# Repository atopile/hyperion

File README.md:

<p align="center">Insanely bright modular LED display</p>

### *** IN DEVELOPMENT ***
Project is currently in development and may not compile with latest compiler.

### Why

Current LED matrix displays are underwhelming: low brightness, low dynamic range, and washed‑out visuals in real venues. Hyperion flips that on its head with ridiculous luminance, high refresh, and a visual language that holds up in fog, dark, and daylight spill.

### Highlights

- **Blinding brightness**: designed to punch through haze and stage lighting
- **High refresh**: > 500 Hz target for artifact‑free motion and strobes
- **Chunky pixels**: 4 LEDs per pixel, **15 mm pitch** for bold geometry
- **Modular**: building full **420 × 420 mm** panels (limited by JLC assembly)
- **Controls**: video stream input (WIP) + DMX for audio‑sync (planned)

### Status

- We’ve built an initial coupon: **60 × 60 mm**, peak measured draw ~ **42 W**
- Driver: Macroblock **MBI5043** current sink
- Power rails: LED 5–17 V, logic 5 V / 3.3 V
- Hardware source is being reconstructed in ato v2 from the pixel upward.
  Pixel, pixel-row, cluster, and cluster-row qualification builds are present;
  the dual-row, controller, and complete panel hierarchy remain in progress.

### Hardware source

The root `ato.yaml` is the ato-v2 project. Physical parts resolve through the
v2 library server rather than vendored component assets. The migration is
validated bottom-up using the individual build targets before each layer is
connected into the full panel.

The shared active-low snake-data enable boundary is modeled separately in
`modules/snake_enable_distribution.ato`: one 3.3 V-to-5 V translator drives
seven 5 V-referenced NC7SZ125 enable inputs and defaults them disabled with a
pull-up.

### Pixel geometry

- **Pitch**: 15 mm → ~66 px/m in each axis → ~4,444 px/m²
- **LEDs per pixel**: 4 (RGBW cluster) → ~17,776 LEDs/m²
- **Look**: deliberately low‑density, high‑punch “big voxel” aesthetic

### How bright is it? A back‑of‑the‑napkin estimate

- Coupon area A = 60 mm × 60 mm = **0.0036 m²**
- Peak power P ≈ **42 W**
- If LED efficacy η ≈ **60–100 lm/W** (RGBW mix, conservative):
  - Luminous exitance M ≈ P·η/A ≈ 0.94–1.17 × 10⁶ lm/m²
  - Luminance L ≈ M/π ≈ **220k–370k nits**
- Compared to MacBook Pro (XDR): typical SDR ~500 nits; HDR sustained ~1,000 nits; peak ~1,600 nits. Hyperion coupon (est.): **~140×–700× brighter** per unit area.
  - Peak power assumes ~1% duty cycle for bright strobe effects or fractional‑panel use; not continuous.

Note: 42 W on 0.0036 m² implies ~11.7 kW/m² at full blast. Scaled to a **3 × 2 m** panel: ~**70–75 kW** peak. This is a thermal and power‑distribution thought experiment, not a duty‑cycle recommendation.

### Light as an underexplored rave medium

Light isn’t just illumination; it’s a volumetric instrument. Hyperion treats photons like sound—sculpted in space, time, and intensity—to cut through haze and occupy the room, not just the wall.

- Spatial volume: beams and voxels that read in fog, from meters away
- Temporal punch: sub‑ms strobes and decay envelopes, not just fades
- Materiality: bold pixels and high luminance over fine‑pitch “screens”
- Emergence: interference, moiré, and wavefronts that breathe with the music

### Roadmap

- Assemble first **420 × 420 mm** panels
- Ingest **video streams** (software pipeline WIP)
- **DMX** input for lighting desk sync and audio‑reactive modes
- Thermal, PSU, and duty‑cycle constraints for safe operation
- Thermal/power R&D: explore bulk energy storage (caps/supercaps) for strobe transients and peak handling
- Distributed temperature sensing across panels (NTC grid or digital sensors) for thermal maps and throttling

### License

MIT

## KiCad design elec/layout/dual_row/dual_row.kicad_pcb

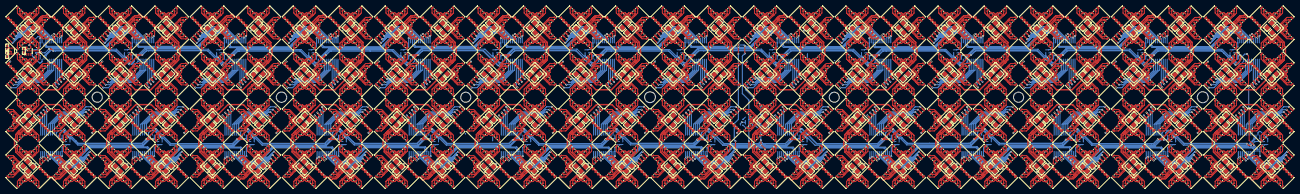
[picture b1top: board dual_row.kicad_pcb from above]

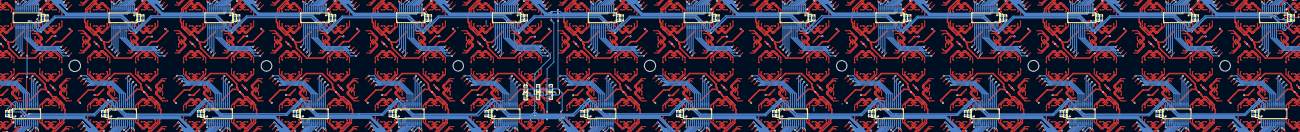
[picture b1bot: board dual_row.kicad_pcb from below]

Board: 2 copper layers, 882 parts (93 on the bottom side), 1856 nets.

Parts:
C1, C2, C3, C4, C5, C6, C7, C8, C10, C11, C12, C13, C14, C15, C16, C17, C19, C20, C21, C22, C23, C24, C25, C26, C28, C29, C30, C31, C32, C33, C34, C35, C37, C38, C39, C40, C41, C42, C43, C44, C46, C47, C48, C49, C50, C51, C52, C53, C55, C56, C57, C58, C59, C60, C61, C62, C64, C65, C66, C67, C68, C69, C70, C71, C73, C74, C75, C76, C77, C78, C79, C80, C82, C83, C84, C85, C86, C87, C88, C89, C91, C92, C93, C94, C95, C96, C97, C98, C100, C101, C102, C103, C104, C105, C106, C107, C109, C110, C111, C112, C113, C114, C115, C116, C118, C119, C120, C121, C122, C123, C124, C125, C127, C128, C129, C130, C131, C132, C133, C134, C136, C137, C138, C139, C140, C141, C142, C143, C145, C146, C147, C148, C149, C150, C151, C152, C154, C155, C156, C157, C158, C159, C160, C161, C163, C164, C165, C166, C167, C168, C169, C170, C172, C173, C174, C175, C176, C177, C178, C179, C181, C182, C183, C184, C185, C186, C187, C188, C190, C191, C192, C193, C194, C195, C196, C197, C199, C200, C201, C202, C203, C204, C205, C206, C208, C209, C210, C211, C212, C213, C214, C215, C217, C218, C219, C220, C221, C222, C223, C224, C226, C227, C228, C229, C230, C231, C232, C233, C235, C236, C237, C238, C239, C240, C241, C242, C244, C245, C246, C247, C248, C249, C250, C251: 10µF ±10% 25V X5R; C0805
C9, C18, C27, C36, C45, C54, C63, C72, C81, C90, C99, C108, C117, C126, C135, C144, C153, C162, C171, C180, C189, C198, C207, C216, C225, C234, C243, C252, C253, C254, C255, C256, C257, C258, C259, C260, C261: 100nF ±10% 16V X7R; C0402
LED1, LED2, LED3, LED4, LED5, LED6, LED7, LED8, LED9, LED10, LED11, LED12, LED13, LED14, LED15, LED16, LED17, LED18, LED19, LED20, LED21, LED22, LED23, LED24, LED25, LED26, LED27, LED28, LED29, LED30, LED31, LED32, LED33, LED34, LED35, LED36, LED37, LED38, LED39, LED40, LED41, LED42, LED43, LED44, LED45, LED46, LED47, LED48, LED49, LED50, LED51, LED52, LED53, LED54, LED55, LED56, LED57, LED58, LED59, LED60, LED61, LED62, LED63, LED64, LED65, LED66, LED67, LED68, LED69, LED70, LED71, LED72, LED73, LED74, LED75, LED76, LED77, LED78, LED79, LED80, LED81, LED82, LED83, LED84, LED85, LED86, LED87, LED88, LED89, LED90, LED91, LED92, LED93, LED94, LED95, LED96, LED97, LED98, LED99, LED100, LED101, LED102, LED103, LED104, LED105, LED106, LED107, LED108, LED109, LED110, LED111, LED112, LED113, LED114, LED115, LED116, LED117, LED118, LED119, LED120, LED121, LED122, LED123, LED124, LED125, LED126, LED127, LED128, LED129, LED130, LED131, LED132, LED133, LED134, LED135, LED136, LED137, LED138, LED139, LED140, LED141, LED142, LED143, LED144, LED145, LED146, LED147, LED148, LED149, LED150, LED151, LED152, LED153, LED154, LED155, LED156, LED157, LED158, LED159, LED160, LED161, LED162, LED163, LED164, LED165, LED166, LED167, LED168, LED169, LED170, LED171, LED172, LED173, LED174, LED175, LED176, LED177, LED178, LED179, LED180, LED181, LED182, LED183, LED184, LED185, LED186, LED187, LED188, LED189, LED190, LED191, LED192, LED193, LED194, LED195, LED196, LED197, LED198, LED199, LED200, LED201, LED202, LED203, LED204, LED205, LED206, LED207, LED208, LED209, LED210, LED211, LED212, LED213, LED214, LED215, LED216, LED217, LED218, LED219, LED220, LED221, LED222, LED223, LED224, LED225, LED226, LED227, LED228, LED229, LED230, LED231, LED232, LED233, LED234, LED235, LED236, LED237, LED238, LED239, LED240, LED241, LED242, LED243, LED244, LED245, LED246, LED247, LED248, LED249, LED250, LED251, LED252, LED253, LED254, LED255, LED256, LED257, LED258, LED259, LED260, LED261, LED262, LED263, LED264, LED265, LED266, LED267, LED268, LED269, LED270, LED271, LED272, LED273, LED274, LED275, LED276, LED277, LED278, LED279, LED280, LED281, LED282, LED283, LED284, LED285, LED286, LED287, LED288, LED289, LED290, LED291, LED292, LED293, LED294, LED295, LED296, LED297, LED298, LED299, LED300, LED301, LED302, LED303, LED304, LED305, LED306, LED307, LED308, LED309, LED310, LED311, LED312, LED313, LED314, LED315, LED316, LED317, LED318, LED319, LED320, LED321, LED322, LED323, LED324, LED325, LED326, LED327, LED328, LED329, LED330, LED331, LED332, LED333, LED334, LED335, LED336, LED337, LED338, LED339, LED340, LED341, LED342, LED343, LED344, LED345, LED346, LED347, LED348, LED349, LED350, LED351, LED352, LED353, LED354, LED355, LED356, LED357, LED358, LED359, LED360, LED361, LED362, LED363, LED364, LED365, LED366, LED367, LED368, LED369, LED370, LED371, LED372, LED373, LED374, LED375, LED376, LED377, LED378, LED379, LED380, LED381, LED382, LED383, LED384, LED385, LED386, LED387, LED388, LED389, LED390, LED391, LED392, LED393, LED394, LED395, LED396, LED397, LED398, LED399, LED400, LED401, LED402, LED403, LED404, LED405, LED406, LED407, LED408, LED409, LED410, LED411, LED412, LED413, LED414, LED415, LED416, LED417, LED418, LED419, LED420, LED421, LED422, LED423, LED424, LED425, LED426, LED427, LED428, LED429, LED430, LED431, LED432, LED433, LED434, LED435, LED436, LED437, LED438, LED439, LED440, LED441, LED442, LED443, LED444, LED445, LED446, LED447, LED448: LED-SMD_8P-L5.0-W5.0-P1.20_HL-5050RGBW-S1-A27
R1, R2, R3, R4, R5, R6, R7, R8, R9, R10, R11, R12, R13, R14, R15, R16, R17, R18, R19, R20, R21, R22, R23, R24, R25, R26, R27, R28: 309Ω ±1% 62.5mW; R0402
U1, U6, U11, U16, U21, U26, U31, U36, U41, U46, U51, U56, U61, U66, U71, U76, U81, U86, U91, U96, U101, U106, U111, U116, U121, U126, U131, U136: SSOP-24_L8.8-W4.0-P0.64-LS6.2-BL
U2, U3, U4, U5, U7, U8, U9, U10, U12, U13, U14, U15, U17, U18, U19, U20, U22, U23, U24, U25, U27, U28, U29, U30, U32, U33, U34, U35, U37, U38, U39, U40, U42, U43, U44, U45, U47, U48, U49, U50, U52, U53, U54, U55, U57, U58, U59, U60, U62, U63, U64, U65, U67, U68, U69, U70, U72, U73, U74, U75, U77, U78, U79, U80, U82, U83, U84, U85, U87, U88, U89, U90, U92, U93, U94, U95, U97, U98, U99, U100, U102, U103, U104, U105, U107, U108, U109, U110, U112, U113, U114, U115, U117, U118, U119, U120, U122, U123, U124, U125, U127, U128, U129, U130, U132, U133, U134, U135, U137, U138, U139, U140: pixel15
U141: SC-70-5_L2.1-W1.3-P0.65-LS2.1-BR
U142, U143, U144, U145: SC-70-6_L2.2-W1.3-P0.65-LS2.1-BR

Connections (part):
DCLK: U1.3, U6.3, U11.3, U16.3, U21.3, U26.3, U31.3, U36.3, U41.3, U46.3, U51.3, U56.3, U61.3, U66.3, U71.3, U76.3, U81.3, U86.3, U91.3, U96.3, U101.3, U106.3, U111.3, U116.3, U121.3, U126.3, U131.3, U136.3, U143.4
GCLK: U1.21, U6.21, U11.21, U16.21, U21.21, U26.21, U31.21, U36.21, U41.21, U46.21, U51.21, U56.21, U61.21, U66.21, U71.21, U76.21, U81.21, U86.21, U91.21, U96.21, U101.21, U106.21, U111.21, U116.21, U121.21, U126.21, U131.21, U136.21, U144.4
LE: U1.4, U6.4, U11.4, U16.4, U21.4, U26.4, U31.4, U36.4, U41.4, U46.4, U51.4, U56.4, U61.4, U66.4, U71.4, U76.4, U81.4, U86.4, U91.4, U96.4, U101.4, U106.4, U111.4, U116.4, U121.4, U126.4, U131.4, U136.4, U145.4
clusters[0]-REXT-0: R1.1, U1.23
clusters[0]-REXT-1: R15.1, U71.23
clusters[1]-REXT-0: R2.1, U6.23
clusters[1]-REXT-1: R16.1, U76.23
clusters[2]-REXT-0: R3.1, U11.23
clusters[2]-REXT-1: R17.1, U81.23
clusters[3]-REXT-0: R4.1, U16.23
clusters[3]-REXT-1: R18.1, U86.23
clusters[4]-REXT-0: R5.1, U21.23
clusters[4]-REXT-1: R19.1, U91.23
clusters[5]-REXT-0: R6.1, U26.23
clusters[5]-REXT-1: R20.1, U96.23
clusters[6]-REXT-0: R7.1, U31.23
clusters[6]-REXT-1: R21.1, U101.23
clusters[7]-REXT-0: R8.1, U36.23
clusters[7]-REXT-1: R22.1, U106.23
clusters[8]-REXT-0: R9.1, U41.23
clusters[8]-REXT-1: R23.1, U111.23
clusters[9]-REXT-0: R10.1, U46.23
clusters[9]-REXT-1: R24.1, U116.23
clusters[10]-REXT-0: R11.1, U51.23
clusters[10]-REXT-1: R25.1, U121.23
clusters[11]-REXT-0: R12.1, U56.23
clusters[11]-REXT-1: R26.1, U126.23
clusters[12]-REXT-0: R13.1, U61.23
clusters[12]-REXT-1: R27.1, U131.23
clusters[13]-REXT-0: R14.1, U66.23
clusters[13]-REXT-1: R28.1, U136.23
data_in-line: U66.22, U71.2
driver-sdo-line-0: U1.22, U6.2
driver-sdo-line-1: U46.22, U51.2
driver-sdo-line-2: U51.22, U56.2
driver-sdo-line-3: U56.22, U61.2
driver-sdo-line-4: U61.22, U66.2
driver-sdo-line-5: U6.22, U11.2
driver-sdo-line-6: U11.22, U16.2
driver-sdo-line-7: U16.22, U21.2
driver-sdo-line-8: U21.22, U26.2
driver-sdo-line-9: U26.22, U31.2
driver-sdo-line-10: U31.22, U36.2
driver-sdo-line-11: U36.22, U41.2
driver-sdo-line-12: U41.22, U46.2
driver-sdo-line-13: U71.22, U76.2
driver-sdo-line-14: U116.22, U121.2
driver-sdo-line-15: U121.22, U126.2
driver-sdo-line-16: U126.22, U131.2
driver-sdo-line-17: U131.22, U136.2
driver-sdo-line-18: U76.22, U81.2
driver-sdo-line-19: U81.22, U86.2
driver-sdo-line-20: U86.22, U91.2
driver-sdo-line-21: U91.22, U96.2
driver-sdo-line-22: U96.22, U101.2
driver-sdo-line-23: U101.22, U106.2
driver-sdo-line-24: U106.22, U111.2
driver-sdo-line-25: U111.22, U116.2
power_a-VCC: C254.1, C256.1, C258.1, C260.1, U142.1, U143.1, U143.5, U144.1, U144.5, U145.1
power_b-GND: C9.2, C18.2, C27.2, C36.2, C45.2, C54.2, C63.2, C72.2, C81.2, C90.2, C99.2, C108.2, C117.2, C126.2, C135.2, C144.2, C153.2, C162.2, C171.2, C180.2, C189.2, C198.2, C207.2, C216.2, C225.2, C234.2, C243.2, C252.2, C253.2, C254.2, C255.2, C256.2, C257.2, C258.2, C259.2, C260.2, C261.2, R1.2, R2.2, R3.2, R4.2, R5.2, R6.2, R7.2, R8.2, R9.2, R10.2, R11.2, R12.2, R13.2, R14.2, R15.2, R16.2, R17.2, R18.2, R19.2, R20.2, R21.2, R22.2, R23.2, R24.2, R25.2, R26.2, R27.2, R28.2, U1.1, U6.1, U11.1, U16.1, U21.1, U26.1, U31.1, U36.1, U41.1, U46.1, U51.1, U56.1, U61.1, U66.1, U71.1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
power_b-VCC: C9.1, C18.1, C27.1, C36.1, C45.1, C54.1, C63.1, C72.1, C81.1, C90.1, C99.1, C108.1, C117.1, C126.1, C135.1, C144.1, C153.1, C162.1, C171.1, C180.1, C189.1, C198.1, C207.1, C216.1, C225.1, C234.1, C243.1, C252.1, C253.1, C255.1, C257.1, C259.1, C261.1, U1.24, U6.24, U11.24, U16.24, U21.24, U26.24, U31.24, U36.24, U41.24, U46.24, U51.24, U56.24, U61.24, U66.24, U71.24, U76.24, U81.24, U86.24, U91.24, U96.24, U101.24, U106.24, U111.24, U116.24, U121.24, U126.24, U131.24, U136.24, U141.5, U142.6, U143.6, U144.6, U145.6
power_leds-GND: C1.2, C2.2, C3.2, C4.2, C5.2, C6.2, C7.2, C8.2, C10.2, C11.2, C12.2, C13.2, C14.2, C15.2, C16.2, C17.2, C19.2, C20.2, C21.2, C22.2, C23.2, C24.2, C25.2, C26.2, C28.2, C29.2, C30.2, C31.2, C32.2, C33.2, C34.2, C35.2, C37.2, C38.2, C39.2, C40.2, C41.2, C42.2, C43.2, C44.2, C46.2, C47.2, C48.2, C49.2, C50.2, C51.2, C52.2, C53.2, C55.2, C56.2, C57.2, C58.2, C59.2, C60.2, C61.2, C62.2, C64.2, C65.2, C66.2, C67.2, C68.2, C69.2, C70.2, C71.2, C73.2, C74.2, C75.2, C76.2, C77.2, C78.2, C79.2, C80.2, C82.2, C83.2, C84.2, C85.2, C86.2, C87.2, C88.2, C89.2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
power_leds-VCC: C1.1, C2.1, C3.1, C4.1, C5.1, C6.1, C7.1, C8.1, C10.1, C11.1, C12.1, C13.1, C14.1, C15.1, C16.1, C17.1, C19.1, C20.1, C21.1, C22.1, C23.1, C24.1, C25.1, C26.1, C28.1, C29.1, C30.1, C31.1, C32.1, C33.1, C34.1, C35.1, C37.1, C38.1, C39.1, C40.1, C41.1, C42.1, C43.1, C44.1, C46.1, C47.1, C48.1, C49.1, C50.1, C51.1, C52.1, C53.1, C55.1, C56.1, C57.1, C58.1, C59.1, C60.1, C61.1, C62.1, C64.1, C65.1, C66.1, C67.1, C68.1, C69.1, C70.1, C71.1, C73.1, C74.1, C75.1, C76.1, C77.1, C78.1, C79.1, C80.1, C82.1, C83.1, C84.1, C85.1, C86.1, C87.1, C88.1, C89.1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
rgbs[1]-anodes-anode-0: LED1.3, LED2.4
rgbs[1]-anodes-anode-1: LED1.1, LED2.2
rgbs[1]-anodes-anode-2: LED1.5, LED2.6
rgbs[1]-anodes-anode-3: LED1.7, LED2.8
rgbs[1]-anodes-anode-4: LED5.3, LED6.4
rgbs[1]-anodes-anode-5: LED5.1, LED6.2
rgbs[1]-anodes-anode-6: LED5.5, LED6.6
rgbs[1]-anodes-anode-7: LED5.7, LED6.8
rgbs[1]-anodes-anode-8: LED9.3, LED10.4
rgbs[1]-anodes-anode-9: LED9.1, LED10.2
rgbs[1]-anodes-anode-10: LED9.5, LED10.6
rgbs[1]-anodes-anode-11: LED9.7, LED10.8
rgbs[1]-anodes-anode-12: LED13.3, LED14.4
rgbs[1]-anodes-anode-13: LED13.1, LED14.2
rgbs[1]-anodes-anode-14: LED13.5, LED14.6
rgbs[1]-anodes-anode-15: LED13.7, LED14.8
rgbs[1]-anodes-anode-16: LED161.3, LED162.4
rgbs[1]-anodes-anode-17: LED161.1, LED162.2
rgbs[1]-anodes-anode-18: LED161.5, LED162.6
rgbs[1]-anodes-anode-19: LED161.7, LED162.8
rgbs[1]-anodes-anode-20: LED165.3, LED166.4
rgbs[1]-anodes-anode-21: LED165.1, LED166.2
rgbs[1]-anodes-anode-22: LED165.5, LED166.6
rgbs[1]-anodes-anode-23: LED165.7, LED166.8
rgbs[1]-anodes-anode-24: LED169.3, LED170.4
rgbs[1]-anodes-anode-25: LED169.1, LED170.2
rgbs[1]-anodes-anode-26: LED169.5, LED170.6
rgbs[1]-anodes-anode-27: LED169.7, LED170.8
rgbs[1]-anodes-anode-28: LED173.3, LED174.4
rgbs[1]-anodes-anode-29: LED173.1, LED174.2
rgbs[1]-anodes-anode-30: LED173.5, LED174.6
rgbs[1]-anodes-anode-31: LED173.7, LED174.8
rgbs[1]-anodes-anode-32: LED177.3, LED178.4
rgbs[1]-anodes-anode-33: LED177.1, LED178.2
rgbs[1]-anodes-anode-34: LED177.5, LED178.6
rgbs[1]-anodes-anode-35: LED177.7, LED178.8
rgbs[1]-anodes-anode-36: LED181.3, LED182.4
rgbs[1]-anodes-anode-37: LED181.1, LED182.2
rgbs[1]-anodes-anode-38: LED181.5, LED182.6
rgbs[1]-anodes-anode-39: LED181.7, LED182.8
rgbs[1]-anodes-anode-40: LED185.3, LED186.4
rgbs[1]-anodes-anode-41: LED185.1, LED186.2
rgbs[1]-anodes-anode-42: LED185.5, LED186.6
rgbs[1]-anodes-anode-43: LED185.7, LED186.8
rgbs[1]-anodes-anode-44: LED189.3, LED190.4
rgbs[1]-anodes-anode-45: LED189.1, LED190.2
rgbs[1]-anodes-anode-46: LED189.5, LED190.6
rgbs[1]-anodes-anode-47: LED189.7, LED190.8
rgbs[1]-anodes-anode-48: LED193.3, LED194.4
rgbs[1]-anodes-anode-49: LED193.1, LED194.2
rgbs[1]-anodes-anode-50: LED193.5, LED194.6
rgbs[1]-anodes-anode-51: LED193.7, LED194.8
rgbs[1]-anodes-anode-52: LED197.3, LED198.4
rgbs[1]-anodes-anode-53: LED197.1, LED198.2
rgbs[1]-anodes-anode-54: LED197.5, LED198.6
rgbs[1]-anodes-anode-55: LED197.7, LED198.8
rgbs[1]-anodes-anode-56: LED201.3, LED202.4
rgbs[1]-anodes-anode-57: LED201.1, LED202.2
rgbs[1]-anodes-anode-58: LED201.5, LED202.6
rgbs[1]-anodes-anode-59: LED201.7, LED202.8
rgbs[1]-anodes-anode-60: LED205.3, LED206.4
rgbs[1]-anodes-anode-61: LED205.1, LED206.2
rgbs[1]-anodes-anode-62: LED205.5, LED206.6
rgbs[1]-anodes-anode-63: LED205.7, LED206.8
rgbs[1]-anodes-anode-64: LED209.3, LED210.4
rgbs[1]-anodes-anode-65: LED209.1, LED210.2
rgbs[1]-anodes-anode-66: LED209.5, LED210.6
rgbs[1]-anodes-anode-67: LED209.7, LED210.8
rgbs[1]-anodes-anode-68: LED213.3, LED214.4
rgbs[1]-anodes-anode-69: LED213.1, LED214.2
rgbs[1]-anodes-anode-70: LED213.5, LED214.6
rgbs[1]-anodes-anode-71: LED213.7, LED214.8
rgbs[1]-anodes-anode-72: LED217.3, LED218.4
rgbs[1]-anodes-anode-73: LED217.1, LED218.2
rgbs[1]-anodes-anode-74: LED217.5, LED218.6
rgbs[1]-anodes-anode-75: LED217.7, LED218.8
rgbs[1]-anodes-anode-76: LED221.3, LED222.4
rgbs[1]-anodes-anode-77: LED221.1, LED222.2
rgbs[1]-anodes-anode-78: LED221.5, LED222.6
rgbs[1]-anodes-anode-79: LED221.7, LED222.8
rgbs[1]-anodes-anode-80: LED17.3, LED18.4
rgbs[1]-anodes-anode-81: LED17.1, LED18.2
rgbs[1]-anodes-anode-82: LED17.5, LED18.6
rgbs[1]-anodes-anode-83: LED17.7, LED18.8
rgbs[1]-anodes-anode-84: LED21.3, LED22.4
rgbs[1]-anodes-anode-85: LED21.1, LED22.2
rgbs[1]-anodes-anode-86: LED21.5, LED22.6
rgbs[1]-anodes-anode-87: LED21.7, LED22.8
rgbs[1]-anodes-anode-88: LED25.3, LED26.4
rgbs[1]-anodes-anode-89: LED25.1, LED26.2
rgbs[1]-anodes-anode-90: LED25.5, LED26.6
rgbs[1]-anodes-anode-91: LED25.7, LED26.8
rgbs[1]-anodes-anode-92: LED29.3, LED30.4
rgbs[1]-anodes-anode-93: LED29.1, LED30.2
rgbs[1]-anodes-anode-94: LED29.5, LED30.6
rgbs[1]-anodes-anode-95: LED29.7, LED30.8
rgbs[1]-anodes-anode-96: LED33.3, LED34.4
rgbs[1]-anodes-anode-97: LED33.1, LED34.2
rgbs[1]-anodes-anode-98: LED33.5, LED34.6
rgbs[1]-anodes-anode-99: LED33.7, LED34.8
rgbs[1]-anodes-anode-100: LED37.3, LED38.4
rgbs[1]-anodes-anode-101: LED37.1, LED38.2
rgbs[1]-anodes-anode-102: LED37.5, LED38.6
rgbs[1]-anodes-anode-103: LED37.7, LED38.8
rgbs[1]-anodes-anode-104: LED41.3, LED42.4
rgbs[1]-anodes-anode-105: LED41.1, LED42.2
rgbs[1]-anodes-anode-106: LED41.5, LED42.6
rgbs[1]-anodes-anode-107: LED41.7, LED42.8
rgbs[1]-anodes-anode-108: LED45.3, LED46.4
rgbs[1]-anodes-anode-109: LED45.1, LED46.2
rgbs[1]-anodes-anode-110: LED45.5, LED46.6
rgbs[1]-anodes-anode-111: LED45.7, LED46.8
rgbs[1]-anodes-anode-112: LED49.3, LED50.4
rgbs[1]-anodes-anode-113: LED49.1, LED50.2
rgbs[1]-anodes-anode-114: LED49.5, LED50.6
rgbs[1]-anodes-anode-115: LED49.7, LED50.8
rgbs[1]-anodes-anode-116: LED53.3, LED54.4
rgbs[1]-anodes-anode-117: LED53.1, LED54.2
rgbs[1]-anodes-anode-118: LED53.5, LED54.6
rgbs[1]-anodes-anode-119: LED53.7, LED54.8
rgbs[1]-anodes-anode-120: LED57.3, LED58.4
rgbs[1]-anodes-anode-121: LED57.1, LED58.2
rgbs[1]-anodes-anode-122: LED57.5, LED58.6
rgbs[1]-anodes-anode-123: LED57.7, LED58.8
rgbs[1]-anodes-anode-124: LED61.3, LED62.4
rgbs[1]-anodes-anode-125: LED61.1, LED62.2
rgbs[1]-anodes-anode-126: LED61.5, LED62.6
rgbs[1]-anodes-anode-127: LED61.7, LED62.8
rgbs[1]-anodes-anode-128: LED65.3, LED66.4
rgbs[1]-anodes-anode-129: LED65.1, LED66.2
rgbs[1]-anodes-anode-130: LED65.5, LED66.6
rgbs[1]-anodes-anode-131: LED65.7, LED66.8
rgbs[1]-anodes-anode-132: LED69.3, LED70.4
rgbs[1]-anodes-anode-133: LED69.1, LED70.2
rgbs[1]-anodes-anode-134: LED69.5, LED70.6
rgbs[1]-anodes-anode-135: LED69.7, LED70.8
rgbs[1]-anodes-anode-136: LED73.3, LED74.4
rgbs[1]-anodes-anode-137: LED73.1, LED74.2
rgbs[1]-anodes-anode-138: LED73.5, LED74.6
rgbs[1]-anodes-anode-139: LED73.7, LED74.8
rgbs[1]-anodes-anode-140: LED77.3, LED78.4
rgbs[1]-anodes-anode-141: LED77.1, LED78.2
rgbs[1]-anodes-anode-142: LED77.5, LED78.6
rgbs[1]-anodes-anode-143: LED77.7, LED78.8
rgbs[1]-anodes-anode-144: LED81.3, LED82.4
rgbs[1]-anodes-anode-145: LED81.1, LED82.2
rgbs[1]-anodes-anode-146: LED81.5, LED82.6
rgbs[1]-anodes-anode-147: LED81.7, LED82.8
rgbs[1]-anodes-anode-148: LED85.3, LED86.4
rgbs[1]-anodes-anode-149: LED85.1, LED86.2
rgbs[1]-anodes-anode-150: LED85.5, LED86.6
rgbs[1]-anodes-anode-151: LED85.7, LED86.8
rgbs[1]-anodes-anode-152: LED89.3, LED90.4
rgbs[1]-anodes-anode-153: LED89.1, LED90.2
rgbs[1]-anodes-anode-154: LED89.5, LED90.6
rgbs[1]-anodes-anode-155: LED89.7, LED90.8
rgbs[1]-anodes-anode-156: LED93.3, LED94.4
rgbs[1]-anodes-anode-157: LED93.1, LED94.2
rgbs[1]-anodes-anode-158: LED93.5, LED94.6
rgbs[1]-anodes-anode-159: LED93.7, LED94.8
rgbs[1]-anodes-anode-160: LED97.3, LED98.4
rgbs[1]-anodes-anode-161: LED97.1, LED98.2
rgbs[1]-anodes-anode-162: LED97.5, LED98.6
rgbs[1]-anodes-anode-163: LED97.7, LED98.8
rgbs[1]-anodes-anode-164: LED101.3, LED102.4
rgbs[1]-anodes-anode-165: LED101.1, LED102.2
rgbs[1]-anodes-anode-166: LED101.5, LED102.6
rgbs[1]-anodes-anode-167: LED101.7, LED102.8
rgbs[1]-anodes-anode-168: LED105.3, LED106.4
rgbs[1]-anodes-anode-169: LED105.1, LED106.2
rgbs[1]-anodes-anode-170: LED105.5, LED106.6
rgbs[1]-anodes-anode-171: LED105.7, LED106.8
rgbs[1]-anodes-anode-172: LED109.3, LED110.4
rgbs[1]-anodes-anode-173: LED109.1, LED110.2
rgbs[1]-anodes-anode-174: LED109.5, LED110.6
rgbs[1]-anodes-anode-175: LED109.7, LED110.8
rgbs[1]-anodes-anode-176: LED113.3, LED114.4
rgbs[1]-anodes-anode-177: LED113.1, LED114.2
rgbs[1]-anodes-anode-178: LED113.5, LED114.6
rgbs[1]-anodes-anode-179: LED113.7, LED114.8
rgbs[1]-anodes-anode-180: LED117.3, LED118.4
rgbs[1]-anodes-anode-181: LED117.1, LED118.2
rgbs[1]-anodes-anode-182: LED117.5, LED118.6
rgbs[1]-anodes-anode-183: LED117.7, LED118.8
rgbs[1]-anodes-anode-184: LED121.3, LED122.4
rgbs[1]-anodes-anode-185: LED121.1, LED122.2
rgbs[1]-anodes-anode-186: LED121.5, LED122.6
rgbs[1]-anodes-anode-187: LED121.7, LED122.8
rgbs[1]-anodes-anode-188: LED125.3, LED126.4
rgbs[1]-anodes-anode-189: LED125.1, LED126.2
rgbs[1]-anodes-anode-190: LED125.5, LED126.6
rgbs[1]-anodes-anode-191: LED125.7, LED126.8
rgbs[1]-anodes-anode-192: LED129.3, LED130.4
rgbs[1]-anodes-anode-193: LED129.1, LED130.2
rgbs[1]-anodes-anode-194: LED129.5, LED130.6
rgbs[1]-anodes-anode-195: LED129.7, LED130.8
rgbs[1]-anodes-anode-196: LED133.3, LED134.4
rgbs[1]-anodes-anode-197: LED133.1, LED134.2
rgbs[1]-anodes-anode-198: LED133.5, LED134.6
rgbs[1]-anodes-anode-199: LED133.7, LED134.8
rgbs[1]-anodes-anode-200: LED137.3, LED138.4
rgbs[1]-anodes-anode-201: LED137.1, LED138.2
rgbs[1]-anodes-anode-202: LED137.5, LED138.6
rgbs[1]-anodes-anode-203: LED137.7, LED138.8
rgbs[1]-anodes-anode-204: LED141.3, LED142.4
rgbs[1]-anodes-anode-205: LED141.1, LED142.2
rgbs[1]-anodes-anode-206: LED141.5, LED142.6
rgbs[1]-anodes-anode-207: LED141.7, LED142.8
rgbs[1]-anodes-anode-208: LED145.3, LED146.4
rgbs[1]-anodes-anode-209: LED145.1, LED146.2
rgbs[1]-anodes-anode-210: LED145.5, LED146.6
rgbs[1]-anodes-anode-211: LED145.7, LED146.8
rgbs[1]-anodes-anode-212: LED149.3, LED150.4
rgbs[1]-anodes-anode-213: LED149.1, LED150.2
rgbs[1]-anodes-anode-214: LED149.5, LED150.6
rgbs[1]-anodes-anode-215: LED149.7, LED150.8
rgbs[1]-anodes-anode-216: LED153.3, LED154.4
rgbs[1]-anodes-anode-217: LED153.1, LED154.2
rgbs[1]-anodes-anode-218: LED153.5, LED154.6
rgbs[1]-anodes-anode-219: LED153.7, LED154.8
rgbs[1]-anodes-anode-220: LED157.3, LED158.4
rgbs[1]-anodes-anode-221: LED157.1, LED158.2
rgbs[1]-anodes-anode-222: LED157.5, LED158.6
rgbs[1]-anodes-anode-223: LED157.7, LED158.8
rgbs[1]-anodes-anode-224: LED225.3, LED226.4
rgbs[1]-anodes-anode-225: LED225.1, LED226.2
rgbs[1]-anodes-anode-226: LED225.5, LED226.6
rgbs[1]-anodes-anode-227: LED225.7, LED226.8
rgbs[1]-anodes-anode-228: LED229.3, LED230.4
rgbs[1]-anodes-anode-229: LED229.1, LED230.2
rgbs[1]-anodes-anode-230: LED229.5, LED230.6
rgbs[1]-anodes-anode-231: LED229.7, LED230.8
rgbs[1]-anodes-anode-232: LED233.3, LED234.4
rgbs[1]-anodes-anode-233: LED233.1, LED234.2
rgbs[1]-anodes-anode-234: LED233.5, LED234.6
rgbs[1]-anodes-anode-235: LED233.7, LED234.8
rgbs[1]-anodes-anode-236: LED237.3, LED238.4
rgbs[1]-anodes-anode-237: LED237.1, LED238.2
rgbs[1]-anodes-anode-238: LED237.5, LED238.6
rgbs[1]-anodes-anode-239: LED237.7, LED238.8
rgbs[1]-anodes-anode-240: LED385.3, LED386.4
rgbs[1]-anodes-anode-241: LED385.1, LED386.2
rgbs[1]-anodes-anode-242: LED385.5, LED386.6
rgbs[1]-anodes-anode-243: LED385.7, LED386.8
rgbs[1]-anodes-anode-244: LED389.3, LED390.4
rgbs[1]-anodes-anode-245: LED389.1, LED390.2
rgbs[1]-anodes-anode-246: LED389.5, LED390.6
rgbs[1]-anodes-anode-247: LED389.7, LED390.8
rgbs[1]-anodes-anode-248: LED393.3, LED394.4
rgbs[1]-anodes-anode-249: LED393.1, LED394.2
rgbs[1]-anodes-anode-250: LED393.5, LED394.6
rgbs[1]-anodes-anode-251: LED393.7, LED394.8
rgbs[1]-anodes-anode-252: LED397.3, LED398.4
rgbs[1]-anodes-anode-253: LED397.1, LED398.2
rgbs[1]-anodes-anode-254: LED397.5, LED398.6
rgbs[1]-anodes-anode-255: LED397.7, LED398.8
rgbs[1]-anodes-anode-256: LED401.3, LED402.4
rgbs[1]-anodes-anode-257: LED401.1, LED402.2
rgbs[1]-anodes-anode-258: LED401.5, LED402.6
rgbs[1]-anodes-anode-259: LED401.7, LED402.8
rgbs[1]-anodes-anode-260: LED405.3, LED406.4
rgbs[1]-anodes-anode-261: LED405.1, LED406.2
rgbs[1]-anodes-anode-262: LED405.5, LED406.6
rgbs[1]-anodes-anode-263: LED405.7, LED406.8
rgbs[1]-anodes-anode-264: LED409.3, LED410.4
rgbs[1]-anodes-anode-265: LED409.1, LED410.2
rgbs[1]-anodes-anode-266: LED409.5, LED410.6
rgbs[1]-anodes-anode-267: LED409.7, LED410.8
rgbs[1]-anodes-anode-268: LED413.3, LED414.4
rgbs[1]-anodes-anode-269: LED413.1, LED414.2
rgbs[1]-anodes-anode-270: LED413.5, LED414.6
rgbs[1]-anodes-anode-271: LED413.7, LED414.8
rgbs[1]-anodes-anode-272: LED417.3, LED418.4
rgbs[1]-anodes-anode-273: LED417.1, LED418.2
rgbs[1]-anodes-anode-274: LED417.5, LED418.6
rgbs[1]-anodes-anode-275: LED417.7, LED418.8
rgbs[1]-anodes-anode-276: LED421.3, LED422.4
rgbs[1]-anodes-anode-277: LED421.1, LED422.2
rgbs[1]-anodes-anode-278: LED421.5, LED422.6
rgbs[1]-anodes-anode-279: LED421.7, LED422.8
rgbs[1]-anodes-anode-280: LED425.3, LED426.4
rgbs[1]-anodes-anode-281: LED425.1, LED426.2
rgbs[1]-anodes-anode-282: LED425.5, LED426.6
rgbs[1]-anodes-anode-283: LED425.7, LED426.8
rgbs[1]-anodes-anode-284: LED429.3, LED430.4
rgbs[1]-anodes-anode-285: LED429.1, LED430.2
rgbs[1]-anodes-anode-286: LED429.5, LED430.6
rgbs[1]-anodes-anode-287: LED429.7, LED430.8
rgbs[1]-anodes-anode-288: LED433.3, LED434.4
rgbs[1]-anodes-anode-289: LED433.1, LED434.2
rgbs[1]-anodes-anode-290: LED433.5, LED434.6
rgbs[1]-anodes-anode-291: LED433.7, LED434.8
rgbs[1]-anodes-anode-292: LED437.3, LED438.4
rgbs[1]-anodes-anode-293: LED437.1, LED438.2
rgbs[1]-anodes-anode-294: LED437.5, LED438.6
rgbs[1]-anodes-anode-295: LED437.7, LED438.8
rgbs[1]-anodes-anode-296: LED441.3, LED442.4
rgbs[1]-anodes-anode-297: LED441.1, LED442.2
rgbs[1]-anodes-anode-298: LED441.5, LED442.6
rgbs[1]-anodes-anode-299: LED441.7, LED442.8
rgbs[1]-anodes-anode-300: LED445.3, LED446.4
rgbs[1]-anodes-anode-301: LED445.1, LED446.2
rgbs[1]-anodes-anode-302: LED445.5, LED446.6
rgbs[1]-anodes-anode-303: LED445.7, LED446.8
rgbs[1]-anodes-anode-304: LED241.3, LED242.4
rgbs[1]-anodes-anode-305: LED241.1, LED242.2
rgbs[1]-anodes-anode-306: LED241.5, LED242.6
rgbs[1]-anodes-anode-307: LED241.7, LED242.8
rgbs[1]-anodes-anode-308: LED245.3, LED246.4
rgbs[1]-anodes-anode-309: LED245.1, LED246.2
rgbs[1]-anodes-anode-310: LED245.5, LED246.6
rgbs[1]-anodes-anode-311: LED245.7, LED246.8
rgbs[1]-anodes-anode-312: LED249.3, LED250.4
rgbs[1]-anodes-anode-313: LED249.1, LED250.2
rgbs[1]-anodes-anode-314: LED249.5, LED250.6
rgbs[1]-anodes-anode-315: LED249.7, LED250.8
rgbs[1]-anodes-anode-316: LED253.3, LED254.4
rgbs[1]-anodes-anode-317: LED253.1, LED254.2
rgbs[1]-anodes-anode-318: LED253.5, LED254.6
rgbs[1]-anodes-anode-319: LED253.7, LED254.8
rgbs[1]-anodes-anode-320: LED257.3, LED258.4
rgbs[1]-anodes-anode-321: LED257.1, LED258.2
rgbs[1]-anodes-anode-322: LED257.5, LED258.6
rgbs[1]-anodes-anode-323: LED257.7, LED258.8
rgbs[1]-anodes-anode-324: LED261.3, LED262.4
rgbs[1]-anodes-anode-325: LED261.1, LED262.2
rgbs[1]-anodes-anode-326: LED261.5, LED262.6
rgbs[1]-anodes-anode-327: LED261.7, LED262.8
rgbs[1]-anodes-anode-328: LED265.3, LED266.4
rgbs[1]-anodes-anode-329: LED265.1, LED266.2
rgbs[1]-anodes-anode-330: LED265.5, LED266.6
rgbs[1]-anodes-anode-331: LED265.7, LED266.8
rgbs[1]-anodes-anode-332: LED269.3, LED270.4
rgbs[1]-anodes-anode-333: LED269.1, LED270.2
rgbs[1]-anodes-anode-334: LED269.5, LED270.6
rgbs[1]-anodes-anode-335: LED269.7, LED270.8
rgbs[1]-anodes-anode-336: LED273.3, LED274.4
rgbs[1]-anodes-anode-337: LED273.1, LED274.2
rgbs[1]-anodes-anode-338: LED273.5, LED274.6
rgbs[1]-anodes-anode-339: LED273.7, LED274.8
rgbs[1]-anodes-anode-340: LED277.3, LED278.4
rgbs[1]-anodes-anode-341: LED277.1, LED278.2
rgbs[1]-anodes-anode-342: LED277.5, LED278.6
rgbs[1]-anodes-anode-343: LED277.7, LED278.8
rgbs[1]-anodes-anode-344: LED281.3, LED282.4
rgbs[1]-anodes-anode-345: LED281.1, LED282.2
rgbs[1]-anodes-anode-346: LED281.5, LED282.6
rgbs[1]-anodes-anode-347: LED281.7, LED282.8
rgbs[1]-anodes-anode-348: LED285.3, LED286.4
rgbs[1]-anodes-anode-349: LED285.1, LED286.2
rgbs[1]-anodes-anode-350: LED285.5, LED286.6
rgbs[1]-anodes-anode-351: LED285.7, LED286.8
rgbs[1]-anodes-anode-352: LED289.3, LED290.4
rgbs[1]-anodes-anode-353: LED289.1, LED290.2
rgbs[1]-anodes-anode-354: LED289.5, LED290.6
rgbs[1]-anodes-anode-355: LED289.7, LED290.8
rgbs[1]-anodes-anode-356: LED293.3, LED294.4
rgbs[1]-anodes-anode-357: LED293.1, LED294.2
rgbs[1]-anodes-anode-358: LED293.5, LED294.6
rgbs[1]-anodes-anode-359: LED293.7, LED294.8
rgbs[1]-anodes-anode-360: LED297.3, LED298.4
rgbs[1]-anodes-anode-361: LED297.1, LED298.2
rgbs[1]-anodes-anode-362: LED297.5, LED298.6
rgbs[1]-anodes-anode-363: LED297.7, LED298.8
rgbs[1]-anodes-anode-364: LED301.3, LED302.4
rgbs[1]-anodes-anode-365: LED301.1, LED302.2
rgbs[1]-anodes-anode-366: LED301.5, LED302.6
rgbs[1]-anodes-anode-367: LED301.7, LED302.8
rgbs[1]-anodes-anode-368: LED305.3, LED306.4
rgbs[1]-anodes-anode-369: LED305.1, LED306.2
rgbs[1]-anodes-anode-370: LED305.5, LED306.6
rgbs[1]-anodes-anode-371: LED305.7, LED306.8
rgbs[1]-anodes-anode-372: LED309.3, LED310.4
rgbs[1]-anodes-anode-373: LED309.1, LED310.2
rgbs[1]-anodes-anode-374: LED309.5, LED310.6
rgbs[1]-anodes-anode-375: LED309.7, LED310.8
rgbs[1]-anodes-anode-376: LED313.3, LED314.4
rgbs[1]-anodes-anode-377: LED313.1, LED314.2
rgbs[1]-anodes-anode-378: LED313.5, LED314.6
rgbs[1]-anodes-anode-379: LED313.7, LED314.8
rgbs[1]-anodes-anode-380: LED317.3, LED318.4
rgbs[1]-anodes-anode-381: LED317.1, LED318.2
rgbs[1]-anodes-anode-382: LED317.5, LED318.6
rgbs[1]-anodes-anode-383: LED317.7, LED318.8
rgbs[1]-anodes-anode-384: LED321.3, LED322.4
rgbs[1]-anodes-anode-385: LED321.1, LED322.2
rgbs[1]-anodes-anode-386: LED321.5, LED322.6
rgbs[1]-anodes-anode-387: LED321.7, LED322.8
rgbs[1]-anodes-anode-388: LED325.3, LED326.4
rgbs[1]-anodes-anode-389: LED325.1, LED326.2
rgbs[1]-anodes-anode-390: LED325.5, LED326.6
rgbs[1]-anodes-anode-391: LED325.7, LED326.8
rgbs[1]-anodes-anode-392: LED329.3, LED330.4
rgbs[1]-anodes-anode-393: LED329.1, LED330.2
rgbs[1]-anodes-anode-394: LED329.5, LED330.6
rgbs[1]-anodes-anode-395: LED329.7, LED330.8
rgbs[1]-anodes-anode-396: LED333.3, LED334.4
rgbs[1]-anodes-anode-397: LED333.1, LED334.2
rgbs[1]-anodes-anode-398: LED333.5, LED334.6
rgbs[1]-anodes-anode-399: LED333.7, LED334.8
rgbs[1]-anodes-anode-400: LED337.3, LED338.4
rgbs[1]-anodes-anode-401: LED337.1, LED338.2
rgbs[1]-anodes-anode-402: LED337.5, LED338.6
rgbs[1]-anodes-anode-403: LED337.7, LED338.8
rgbs[1]-anodes-anode-404: LED341.3, LED342.4
rgbs[1]-anodes-anode-405: LED341.1, LED342.2
rgbs[1]-anodes-anode-406: LED341.5, LED342.6
rgbs[1]-anodes-anode-407: LED341.7, LED342.8
rgbs[1]-anodes-anode-408: LED345.3, LED346.4
rgbs[1]-anodes-anode-409: LED345.1, LED346.2
rgbs[1]-anodes-anode-410: LED345.5, LED346.6
rgbs[1]-anodes-anode-411: LED345.7, LED346.8
rgbs[1]-anodes-anode-412: LED349.3, LED350.4
rgbs[1]-anodes-anode-413: LED349.1, LED350.2
rgbs[1]-anodes-anode-414: LED349.5, LED350.6
rgbs[1]-anodes-anode-415: LED349.7, LED350.8
rgbs[1]-anodes-anode-416: LED353.3, LED354.4
rgbs[1]-anodes-anode-417: LED353.1, LED354.2
rgbs[1]-anodes-anode-418: LED353.5, LED354.6
rgbs[1]-anodes-anode-419: LED353.7, LED354.8
rgbs[1]-anodes-anode-420: LED357.3, LED358.4
rgbs[1]-anodes-anode-421: LED357.1, LED358.2
rgbs[1]-anodes-anode-422: LED357.5, LED358.6
rgbs[1]-anodes-anode-423: LED357.7, LED358.8
rgbs[1]-anodes-anode-424: LED361.3, LED362.4
rgbs[1]-anodes-anode-425: LED361.1, LED362.2
rgbs[1]-anodes-anode-426: LED361.5, LED362.6
rgbs[1]-anodes-anode-427: LED361.7, LED362.8
rgbs[1]-anodes-anode-428: LED365.3, LED366.4
rgbs[1]-anodes-anode-429: LED365.1, LED366.2
rgbs[1]-anodes-anode-430: LED365.5, LED366.6
rgbs[1]-anodes-anode-431: LED365.7, LED366.8
rgbs[1]-anodes-anode-432: LED369.3, LED370.4
rgbs[1]-anodes-anode-433: LED369.1, LED370.2
rgbs[1]-anodes-anode-434: LED369.5, LED370.6
rgbs[1]-anodes-anode-435: LED369.7, LED370.8
rgbs[1]-anodes-anode-436: LED373.3, LED374.4
rgbs[1]-anodes-anode-437: LED373.1, LED374.2
rgbs[1]-anodes-anode-438: LED373.5, LED374.6
rgbs[1]-anodes-anode-439: LED373.7, LED374.8
rgbs[1]-anodes-anode-440: LED377.3, LED378.4
rgbs[1]-anodes-anode-441: LED377.1, LED378.2
rgbs[1]-anodes-anode-442: LED377.5, LED378.6
rgbs[1]-anodes-anode-443: LED377.7, LED378.8
rgbs[1]-anodes-anode-444: LED381.3, LED382.4
rgbs[1]-anodes-anode-445: LED381.1, LED382.2
rgbs[1]-anodes-anode-446: LED381.5, LED382.6
rgbs[1]-anodes-anode-447: LED381.7, LED382.8
rgbs[2]-anodes-anode-0: LED2.3, LED3.4
rgbs[2]-anodes-anode-1: LED2.1, LED3.2
rgbs[2]-anodes-anode-2: LED2.5, LED3.6
rgbs[2]-anodes-anode-3: LED2.7, LED3.8
rgbs[2]-anodes-anode-4: LED6.3, LED7.4
rgbs[2]-anodes-anode-5: LED6.1, LED7.2
rgbs[2]-anodes-anode-6: LED6.5, LED7.6
rgbs[2]-anodes-anode-7: LED6.7, LED7.8
rgbs[2]-anodes-anode-8: LED10.3, LED11.4
rgbs[2]-anodes-anode-9: LED10.1, LED11.2
rgbs[2]-anodes-anode-10: LED10.5, LED11.6
rgbs[2]-anodes-anode-11: LED10.7, LED11.8
rgbs[2]-anodes-anode-12: LED14.3, LED15.4
rgbs[2]-anodes-anode-13: LED14.1, LED15.2
rgbs[2]-anodes-anode-14: LED14.5, LED15.6
rgbs[2]-anodes-anode-15: LED14.7, LED15.8
rgbs[2]-anodes-anode-16: LED162.3, LED163.4
rgbs[2]-anodes-anode-17: LED162.1, LED163.2
rgbs[2]-anodes-anode-18: LED162.5, LED163.6
rgbs[2]-anodes-anode-19: LED162.7, LED163.8
rgbs[2]-anodes-anode-20: LED166.3, LED167.4
rgbs[2]-anodes-anode-21: LED166.1, LED167.2
rgbs[2]-anodes-anode-22: LED166.5, LED167.6
rgbs[2]-anodes-anode-23: LED166.7, LED167.8
rgbs[2]-anodes-anode-24: LED170.3, LED171.4
rgbs[2]-anodes-anode-25: LED170.1, LED171.2
rgbs[2]-anodes-anode-26: LED170.5, LED171.6
rgbs[2]-anodes-anode-27: LED170.7, LED171.8
rgbs[2]-anodes-anode-28: LED174.3, LED175.4
rgbs[2]-anodes-anode-29: LED174.1, LED175.2
rgbs[2]-anodes-anode-30: LED174.5, LED175.6
rgbs[2]-anodes-anode-31: LED174.7, LED175.8
rgbs[2]-anodes-anode-32: LED178.3, LED179.4
rgbs[2]-anodes-anode-33: LED178.1, LED179.2
rgbs[2]-anodes-anode-34: LED178.5, LED179.6
rgbs[2]-anodes-anode-35: LED178.7, LED179.8
rgbs[2]-anodes-anode-36: LED182.3, LED183.4
rgbs[2]-anodes-anode-37: LED182.1, LED183.2
rgbs[2]-anodes-anode-38: LED182.5, LED183.6
rgbs[2]-anodes-anode-39: LED182.7, LED183.8
rgbs[2]-anodes-anode-40: LED186.3, LED187.4
rgbs[2]-anodes-anode-41: LED186.1, LED187.2
rgbs[2]-anodes-anode-42: LED186.5, LED187.6
rgbs[2]-anodes-anode-43: LED186.7, LED187.8
rgbs[2]-anodes-anode-44: LED190.3, LED191.4
rgbs[2]-anodes-anode-45: LED190.1, LED191.2
rgbs[2]-anodes-anode-46: LED190.5, LED191.6
rgbs[2]-anodes-anode-47: LED190.7, LED191.8
rgbs[2]-anodes-anode-48: LED194.3, LED195.4
rgbs[2]-anodes-anode-49: LED194.1, LED195.2
rgbs[2]-anodes-anode-50: LED194.5, LED195.6
rgbs[2]-anodes-anode-51: LED194.7, LED195.8
rgbs[2]-anodes-anode-52: LED198.3, LED199.4
rgbs[2]-anodes-anode-53: LED198.1, LED199.2
rgbs[2]-anodes-anode-54: LED198.5, LED199.6
rgbs[2]-anodes-anode-55: LED198.7, LED199.8
rgbs[2]-anodes-anode-56: LED202.3, LED203.4
rgbs[2]-anodes-anode-57: LED202.1, LED203.2
rgbs[2]-anodes-anode-58: LED202.5, LED203.6
rgbs[2]-anodes-anode-59: LED202.7, LED203.8
rgbs[2]-anodes-anode-60: LED206.3, LED207.4
rgbs[2]-anodes-anode-61: LED206.1, LED207.2
rgbs[2]-anodes-anode-62: LED206.5, LED207.6
rgbs[2]-anodes-anode-63: LED206.7, LED207.8
rgbs[2]-anodes-anode-64: LED210.3, LED211.4
rgbs[2]-anodes-anode-65: LED210.1, LED211.2
rgbs[2]-anodes-anode-66: LED210.5, LED211.6
rgbs[2]-anodes-anode-67: LED210.7, LED211.8
rgbs[2]-anodes-anode-68: LED214.3, LED215.4
rgbs[2]-anodes-anode-69: LED214.1, LED215.2
rgbs[2]-anodes-anode-70: LED214.5, LED215.6
rgbs[2]-anodes-anode-71: LED214.7, LED215.8
rgbs[2]-anodes-anode-72: LED218.3, LED219.4
rgbs[2]-anodes-anode-73: LED218.1, LED219.2
rgbs[2]-anodes-anode-74: LED218.5, LED219.6
rgbs[2]-anodes-anode-75: LED218.7, LED219.8
rgbs[2]-anodes-anode-76: LED222.3, LED223.4
rgbs[2]-anodes-anode-77: LED222.1, LED223.2
rgbs[2]-anodes-anode-78: LED222.5, LED223.6
rgbs[2]-anodes-anode-79: LED222.7, LED223.8
rgbs[2]-anodes-anode-80: LED18.3, LED19.4
rgbs[2]-anodes-anode-81: LED18.1, LED19.2
rgbs[2]-anodes-anode-82: LED18.5, LED19.6
rgbs[2]-anodes-anode-83: LED18.7, LED19.8
rgbs[2]-anodes-anode-84: LED22.3, LED23.4
rgbs[2]-anodes-anode-85: LED22.1, LED23.2
rgbs[2]-anodes-anode-86: LED22.5, LED23.6
rgbs[2]-anodes-anode-87: LED22.7, LED23.8
rgbs[2]-anodes-anode-88: LED26.3, LED27.4
rgbs[2]-anodes-anode-89: LED26.1, LED27.2
rgbs[2]-anodes-anode-90: LED26.5, LED27.6
rgbs[2]-anodes-anode-91: LED26.7, LED27.8
rgbs[2]-anodes-anode-92: LED30.3, LED31.4
rgbs[2]-anodes-anode-93: LED30.1, LED31.2
rgbs[2]-anodes-anode-94: LED30.5, LED31.6
rgbs[2]-anodes-anode-95: LED30.7, LED31.8
rgbs[2]-anodes-anode-96: LED34.3, LED35.4
rgbs[2]-anodes-anode-97: LED34.1, LED35.2
rgbs[2]-anodes-anode-98: LED34.5, LED35.6
rgbs[2]-anodes-anode-99: LED34.7, LED35.8
rgbs[2]-anodes-anode-100: LED38.3, LED39.4
rgbs[2]-anodes-anode-101: LED38.1, LED39.2
rgbs[2]-anodes-anode-102: LED38.5, LED39.6
rgbs[2]-anodes-anode-103: LED38.7, LED39.8
rgbs[2]-anodes-anode-104: LED42.3, LED43.4
rgbs[2]-anodes-anode-105: LED42.1, LED43.2
rgbs[2]-anodes-anode-106: LED42.5, LED43.6
rgbs[2]-anodes-anode-107: LED42.7, LED43.8
rgbs[2]-anodes-anode-108: LED46.3, LED47.4
rgbs[2]-anodes-anode-109: LED46.1, LED47.2
rgbs[2]-anodes-anode-110: LED46.5, LED47.6
rgbs[2]-anodes-anode-111: LED46.7, LED47.8
rgbs[2]-anodes-anode-112: LED50.3, LED51.4
rgbs[2]-anodes-anode-113: LED50.1, LED51.2
rgbs[2]-anodes-anode-114: LED50.5, LED51.6
rgbs[2]-anodes-anode-115: LED50.7, LED51.8
rgbs[2]-anodes-anode-116: LED54.3, LED55.4
rgbs[2]-anodes-anode-117: LED54.1, LED55.2
rgbs[2]-anodes-anode-118: LED54.5, LED55.6
rgbs[2]-anodes-anode-119: LED54.7, LED55.8
rgbs[2]-anodes-anode-120: LED58.3, LED59.4
rgbs[2]-anodes-anode-121: LED58.1, LED59.2
rgbs[2]-anodes-anode-122: LED58.5, LED59.6
rgbs[2]-anodes-anode-123: LED58.7, LED59.8
rgbs[2]-anodes-anode-124: LED62.3, LED63.4
rgbs[2]-anodes-anode-125: LED62.1, LED63.2
rgbs[2]-anodes-anode-126: LED62.5, LED63.6
rgbs[2]-anodes-anode-127: LED62.7, LED63.8
rgbs[2]-anodes-anode-128: LED66.3, LED67.4
rgbs[2]-anodes-anode-129: LED66.1, LED67.2
rgbs[2]-anodes-anode-130: LED66.5, LED67.6
rgbs[2]-anodes-anode-131: LED66.7, LED67.8
rgbs[2]-anodes-anode-132: LED70.3, LED71.4
rgbs[2]-anodes-anode-133: LED70.1, LED71.2
rgbs[2]-anodes-anode-134: LED70.5, LED71.6
rgbs[2]-anodes-anode-135: LED70.7, LED71.8
rgbs[2]-anodes-anode-136: LED74.3, LED75.4
rgbs[2]-anodes-anode-137: LED74.1, LED75.2
rgbs[2]-anodes-anode-138: LED74.5, LED75.6
rgbs[2]-anodes-anode-139: LED74.7, LED75.8
rgbs[2]-anodes-anode-140: LED78.3, LED79.4
rgbs[2]-anodes-anode-141: LED78.1, LED79.2
rgbs[2]-anodes-anode-142: LED78.5, LED79.6
rgbs[2]-anodes-anode-143: LED78.7, LED79.8
rgbs[2]-anodes-anode-144: LED82.3, LED83.4
rgbs[2]-anodes-anode-145: LED82.1, LED83.2
rgbs[2]-anodes-anode-146: LED82.5, LED83.6
rgbs[2]-anodes-anode-147: LED82.7, LED83.8
rgbs[2]-anodes-anode-148: LED86.3, LED87.4
rgbs[2]-anodes-anode-149: LED86.1, LED87.2
rgbs[2]-anodes-anode-150: LED86.5, LED87.6
rgbs[2]-anodes-anode-151: LED86.7, LED87.8
rgbs[2]-anodes-anode-152: LED90.3, LED91.4
rgbs[2]-anodes-anode-153: LED90.1, LED91.2
rgbs[2]-anodes-anode-154: LED90.5, LED91.6
rgbs[2]-anodes-anode-155: LED90.7, LED91.8
rgbs[2]-anodes-anode-156: LED94.3, LED95.4
rgbs[2]-anodes-anode-157: LED94.1, LED95.2
rgbs[2]-anodes-anode-158: LED94.5, LED95.6
rgbs[2]-anodes-anode-159: LED94.7, LED95.8
rgbs[2]-anodes-anode-160: LED98.3, LED99.4
rgbs[2]-anodes-anode-161: LED98.1, LED99.2
rgbs[2]-anodes-anode-162: LED98.5, LED99.6
rgbs[2]-anodes-anode-163: LED98.7, LED99.8
rgbs[2]-anodes-anode-164: LED102.3, LED103.4
rgbs[2]-anodes-anode-165: LED102.1, LED103.2
rgbs[2]-anodes-anode-166: LED102.5, LED103.6
rgbs[2]-anodes-anode-167: LED102.7, LED103.8
rgbs[2]-anodes-anode-168: LED106.3, LED107.4
rgbs[2]-anodes-anode-169: LED106.1, LED107.2
rgbs[2]-anodes-anode-170: LED106.5, LED107.6
rgbs[2]-anodes-anode-171: LED106.7, LED107.8
rgbs[2]-anodes-anode-172: LED110.3, LED111.4
rgbs[2]-anodes-anode-173: LED110.1, LED111.2
rgbs[2]-anodes-anode-174: LED110.5, LED111.6
rgbs[2]-anodes-anode-175: LED110.7, LED111.8
rgbs[2]-anodes-anode-176: LED114.3, LED115.4
rgbs[2]-anodes-anode-177: LED114.1, LED115.2
rgbs[2]-anodes-anode-178: LED114.5, LED115.6
rgbs[2]-anodes-anode-179: LED114.7, LED115.8
rgbs[2]-anodes-anode-180: LED118.3, LED119.4
rgbs[2]-anodes-anode-181: LED118.1, LED119.2
rgbs[2]-anodes-anode-182: LED118.5, LED119.6
rgbs[2]-anodes-anode-183: LED118.7, LED119.8
rgbs[2]-anodes-anode-184: LED122.3, LED123.4
rgbs[2]-anodes-anode-185: LED122.1, LED123.2
rgbs[2]-anodes-anode-186: LED122.5, LED123.6
rgbs[2]-anodes-anode-187: LED122.7, LED123.8
rgbs[2]-anodes-anode-188: LED126.3, LED127.4
rgbs[2]-anodes-anode-189: LED126.1, LED127.2
rgbs[2]-anodes-anode-190: LED126.5, LED127.6
rgbs[2]-anodes-anode-191: LED126.7, LED127.8
rgbs[2]-anodes-anode-192: LED130.3, LED131.4
rgbs[2]-anodes-anode-193: LED130.1, LED131.2
rgbs[2]-anodes-anode-194: LED130.5, LED131.6
rgbs[2]-anodes-anode-195: LED130.7, LED131.8
rgbs[2]-anodes-anode-196: LED134.3, LED135.4
rgbs[2]-anodes-anode-197: LED134.1, LED135.2
rgbs[2]-anodes-anode-198: LED134.5, LED135.6
rgbs[2]-anodes-anode-199: LED134.7, LED135.8
rgbs[2]-anodes-anode-200: LED138.3, LED139.4
rgbs[2]-anodes-anode-201: LED138.1, LED139.2
rgbs[2]-anodes-anode-202: LED138.5, LED139.6
rgbs[2]-anodes-anode-203: LED138.7, LED139.8
rgbs[2]-anodes-anode-204: LED142.3, LED143.4
rgbs[2]-anodes-anode-205: LED142.1, LED143.2
rgbs[2]-anodes-anode-206: LED142.5, LED143.6
rgbs[2]-anodes-anode-207: LED142.7, LED143.8
rgbs[2]-anodes-anode-208: LED146.3, LED147.4
rgbs[2]-anodes-anode-209: LED146.1, LED147.2
rgbs[2]-anodes-anode-210: LED146.5, LED147.6
rgbs[2]-anodes-anode-211: LED146.7, LED147.8
rgbs[2]-anodes-anode-212: LED150.3, LED151.4
rgbs[2]-anodes-anode-213: LED150.1, LED151.2
rgbs[2]-anodes-anode-214: LED150.5, LED151.6
rgbs[2]-anodes-anode-215: LED150.7, LED151.8
rgbs[2]-anodes-anode-216: LED154.3, LED155.4
rgbs[2]-anodes-anode-217: LED154.1, LED155.2
rgbs[2]-anodes-anode-218: LED154.5, LED155.6
rgbs[2]-anodes-anode-219: LED154.7, LED155.8
rgbs[2]-anodes-anode-220: LED158.3, LED159.4
rgbs[2]-anodes-anode-221: LED158.1, LED159.2
rgbs[2]-anodes-anode-222: LED158.5, LED159.6
rgbs[2]-anodes-anode-223: LED158.7, LED159.8
rgbs[2]-anodes-anode-224: LED226.3, LED227.4
rgbs[2]-anodes-anode-225: LED226.1, LED227.2
rgbs[2]-anodes-anode-226: LED226.5, LED227.6
rgbs[2]-anodes-anode-227: LED226.7, LED227.8
rgbs[2]-anodes-anode-228: LED230.3, LED231.4
rgbs[2]-anodes-anode-229: LED230.1, LED231.2
rgbs[2]-anodes-anode-230: LED230.5, LED231.6
rgbs[2]-anodes-anode-231: LED230.7, LED231.8
rgbs[2]-anodes-anode-232: LED234.3, LED235.4
rgbs[2]-anodes-anode-233: LED234.1, LED235.2
rgbs[2]-anodes-anode-234: LED234.5, LED235.6
rgbs[2]-anodes-anode-235: LED234.7, LED235.8
rgbs[2]-anodes-anode-236: LED238.3, LED239.4
rgbs[2]-anodes-anode-237: LED238.1, LED239.2
rgbs[2]-anodes-anode-238: LED238.5, LED239.6
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
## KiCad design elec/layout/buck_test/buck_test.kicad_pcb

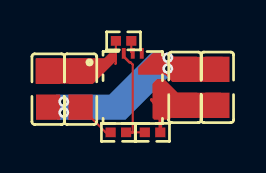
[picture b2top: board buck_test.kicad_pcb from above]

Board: 2 copper layers, 8 parts (0 on the bottom side), 5 nets.

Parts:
C1, C2: 10µF ±10% 25V X7R; C0805
C3, C4: 22µF ±20% 10V X7R; C0805
R1, R3: 10kΩ ±1% 62.5mW; R0402
R2: 1.37kΩ ±1% 62.5mW; R0402
U1: QFN-7_L4.0-W3.3_TPSM863257RDXR

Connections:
EN: R1.2, U1.6
GND: C1.2, C2.2, C3.2, C4.2, R2.2, U1.4
VDIV_OUTPUT: R2.1, R3.2, U1.7
power-VCC: C3.1, C4.1, R3.1, U1.3
power_in-VCC: C1.1, C2.1, R1.1, U1.1

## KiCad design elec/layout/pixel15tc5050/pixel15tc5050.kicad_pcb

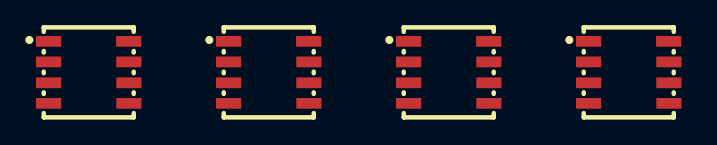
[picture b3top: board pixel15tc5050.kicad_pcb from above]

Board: 2 copper layers, 5 parts (0 on the bottom side), 13 nets, no tracks yet.

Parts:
LED1, LED2, LED3, LED4: LED-SMD_8P-L5.0-W5.0-TL-FD
U1: pixel15

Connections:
rgbs[0]-anodes-anode: LED1.1, LED1.2, LED1.3, LED1.4
rgbs[1]-anodes-anode-0: LED1.6, LED2.3
rgbs[1]-anodes-anode-1: LED1.5, LED2.4
rgbs[1]-anodes-anode-2: LED1.7, LED2.2
rgbs[1]-anodes-anode-3: LED1.8, LED2.1
rgbs[2]-anodes-anode-0: LED2.6, LED3.3
rgbs[2]-anodes-anode-1: LED2.5, LED3.4
rgbs[2]-anodes-anode-2: LED2.7, LED3.2
rgbs[2]-anodes-anode-3: LED2.8, LED3.1
rgbs[3]-anodes-anode-0: LED3.6, LED4.3
rgbs[3]-anodes-anode-1: LED3.5, LED4.4
rgbs[3]-anodes-anode-2: LED3.7, LED4.2
rgbs[3]-anodes-anode-3: LED3.8, LED4.1

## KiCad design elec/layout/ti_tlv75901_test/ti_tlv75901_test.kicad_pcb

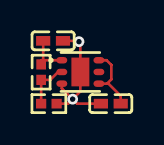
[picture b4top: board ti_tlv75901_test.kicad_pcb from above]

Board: 2 copper layers, 5 parts (0 on the bottom side), 4 nets.

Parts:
C1, C2: 1µF ±10% 25V X5R; C0402
R1: 10kΩ ±1% 62.5mW; R0402
R2: 51kΩ ±1% 62.5mW; R0402
U1: WSON-6_L2.0-W2.0-P0.65-TL-EP

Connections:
GND: C1.2, C2.2, R1.2, U1.3, U1.7
VDIV_OUTPUT: R1.1, R2.2, U1.2
power_in-VCC: C1.1, U1.4, U1.6
power_out-VCC: C2.1, R2.1, U1.1

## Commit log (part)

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2025-08-01 Init commit
2025-08-01 pixel demos
2025-08-01 Pixel15 & Cluster
2025-08-01 pixel10hl5050 routing
2025-08-02 pixel refactor
2025-08-02 cluster with driver
2025-08-02 broken kicad file
2025-08-02 cluster fix up
2025-08-03 shipped board
2025-08-15 built this
2025-08-15 first stab at firmware
2025-08-16 working
2025-08-16 ready for animations
2025-08-16 splitting colors
2025-08-16 reorg
2025-08-16 arduino -> pico-sdk
2025-08-16 refactor
2025-08-16 set_image()
2025-08-16 checkerboard
2025-08-16 toggle animation with button
2025-08-16 kinda working
2025-08-18 checking in driver
2025-08-19 updating rp2040
2025-08-20 add pannel render
2025-08-20 update pannel size
2025-08-22 tight layout
2025-08-22 add strobe animations
2025-08-22 fix 3rd pixel color reversal
2025-08-30 cheat build 49 clusters no layout
2025-09-05 init effectsim
2025-09-06 fixed mapping; server-driven geometry
2025-09-06 led layout masking
2025-09-06 branding
2025-09-06 fix 2x clients
2025-09-06 circular LEDs with lens flare
2025-09-08 webgl renderer
2025-09-08 rm spec
2025-09-12 pick syntax
2025-09-12 switch to has_explicit_part for explicit picks
2025-09-12 build
2025-09-13 layout row
2025-09-13 wire up cluster row
2025-09-19 column and panel layout
2025-09-19 move around
2025-09-20 friday checkin
2025-09-26 layout checkin
2025-09-27 progress
2025-11-07 layout progress
2025-11-07 checkin
2025-11-07 pick new parts
2025-11-21 compressed PCB as ordered 2025-Nov-21
2025-11-21 chore: stage local updates
